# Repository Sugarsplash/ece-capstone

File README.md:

# ece-capstone
Intel sponsored irrigation project.

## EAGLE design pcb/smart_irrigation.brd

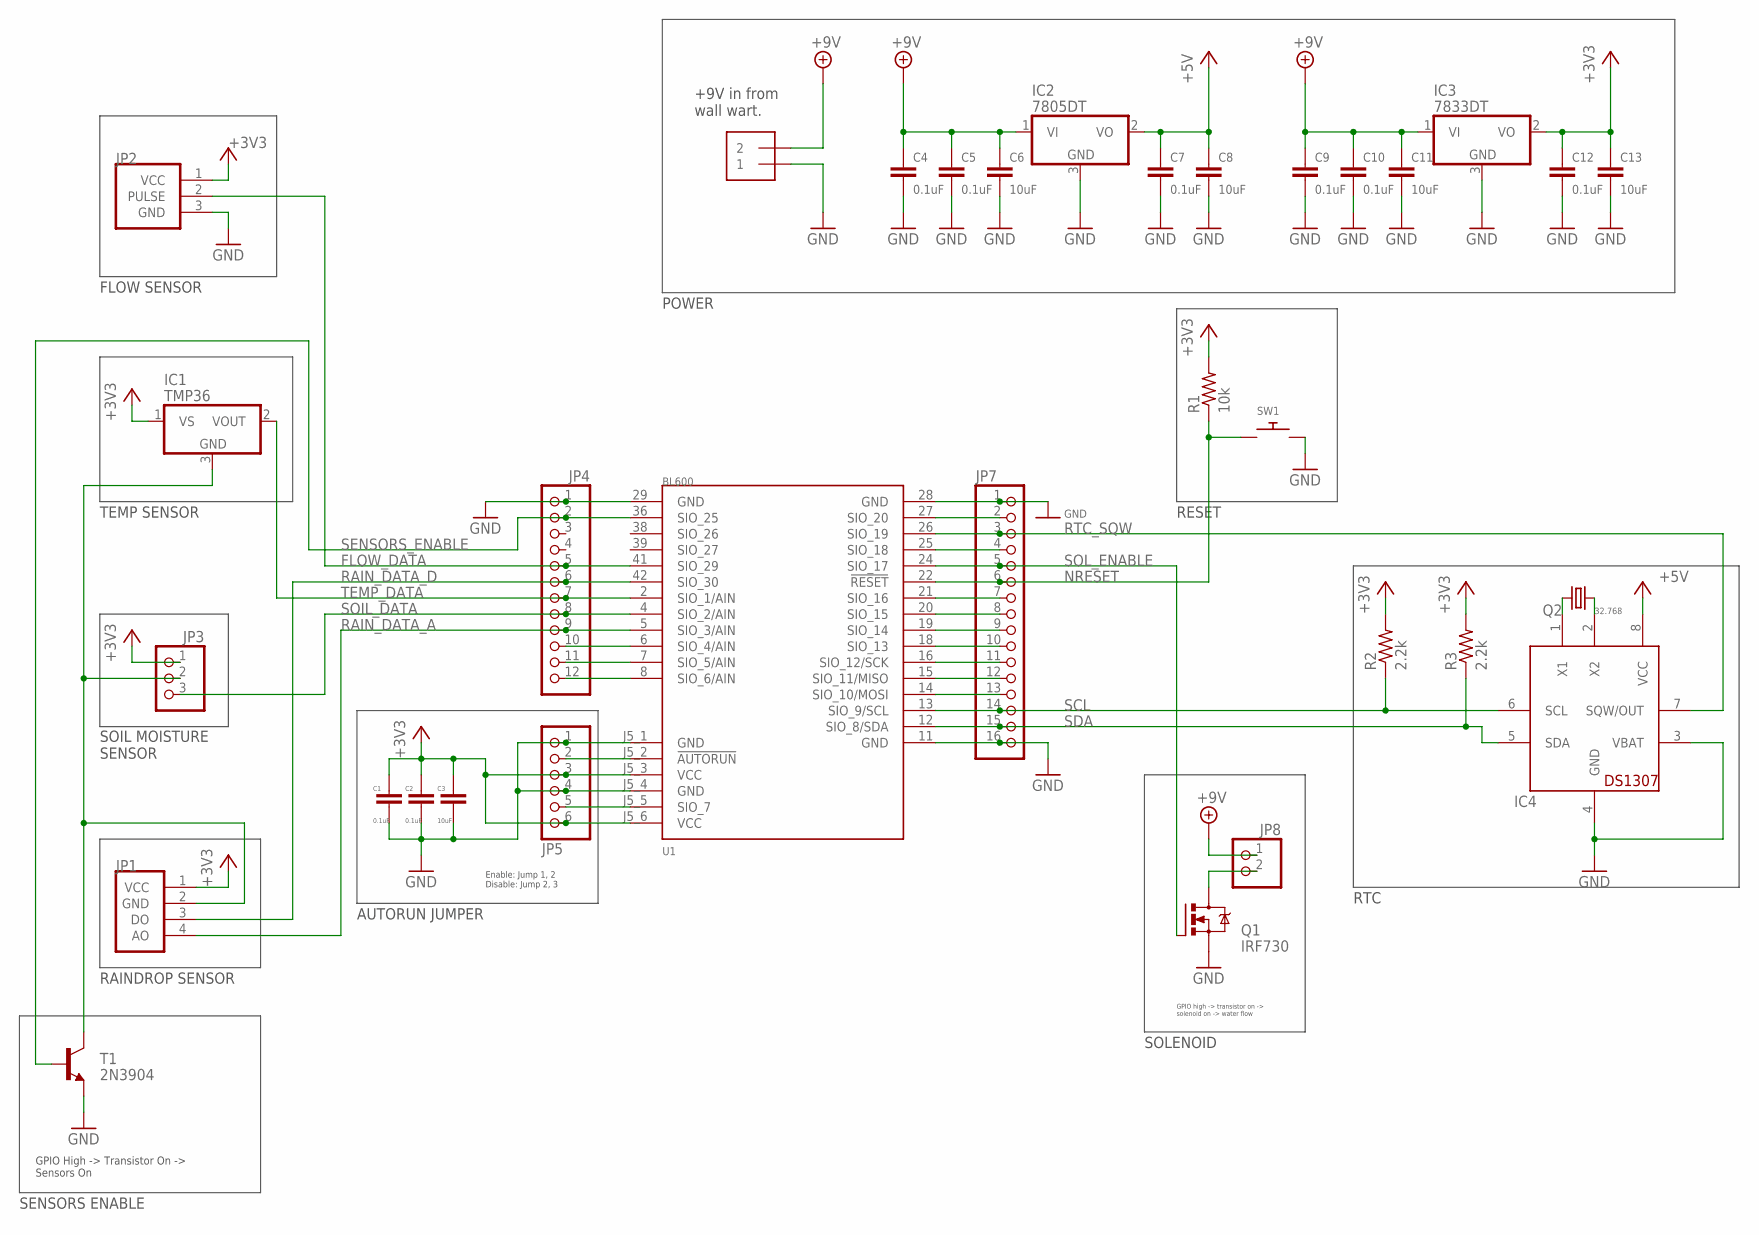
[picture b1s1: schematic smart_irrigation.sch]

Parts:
C1, C2, C4, C5, C7, C9, C10, C12: 0.1uF; C0805
C3, C6, C8, C11, C13: 10uF; C0805
IC1: TMP36; TO92
IC2: 7805DT; TO252
IC3: 7833DT; TO252
IC4: DS1307; DIL08
JP1: RAINDROP; 1X04
JP2: FLOW; 1X03
JP3: PINHD-1X3; 1X03
JP4: PINHD-1X12; 1X12
JP5: PINHD-1X6; 1X06
JP6: 1X2-3.5MM
JP7: PINHD-1X16; 1X16
JP8: PINHD-1X2; 1X02
Q1: IRF730; TO220
Q2: 32.768; TC38H
R1: 10k; M0805
R2, R3: 2.2k; M0805
SW1: SWITCH_PUSHBUTTONEVQ-PE; TACT_PANA-EVQ
T1: 2N3904; TO92
U1: BL600; BOB

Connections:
3V3_TRAN_COL: IC1.3 (GND), JP1.2 (GND), JP3.2, T1.1 (C)
+3V3: C1.1, C2.1, C3.1, C12.1, C13.1, IC1.1 (VS), IC3.2 (VO), JP1.1 (VCC), JP2.1 (VCC), JP3.1, JP5.3, JP5.6, R1.2, R2.2, R3.2, U1.J5_3 (VCC), U1.J5_6 (VCC)
+5V: C7.1, C8.1, IC2.2 (VO), IC4.8 (VCC)
+9V: C4.1, C5.1, C6.1, C9.1, C10.1, C11.1, IC2.1 (VI), IC3.1 (VI), JP6.2, JP8.1
FLOW_DATA: JP2.2 (PULSE), JP4.5, U1.41 (SIO_29)
GND: C1.2, C2.2, C3.2, C4.2, C5.2, C6.2, C7.2, C8.2, C9.2, C10.2, C11.2, C12.2, C13.2, IC2.3 (GND), IC3.3 (GND), IC4.3 (VBAT), IC4.4 (GND), JP2.3 (GND), JP4.1, JP5.1, JP5.4, JP6.1, JP7.1, JP7.16, Q1.S, SW1.P$2, T1.3 (E), U1.11 (GND), U1.28 (GND), U1.29 (GND), U1.J5_1 (GND), U1.J5_4 (GND)
unnamed: IC4.1 (X1), Q2.2
unnamed: IC4.2 (X2), Q2.1
NAUTORUN: JP5.2, U1.J5_2 (!AUTORUN)
NRESET: JP7.6, R1.1, SW1.P$1, U1.22 (!RESET)
RAIN_DATA_A: JP1.4 (AO), JP4.9, U1.5 (SIO_3/AIN)
RAIN_DATA_D: JP1.3 (DO), JP4.6, U1.42 (SIO_30)
RTC_SQW: IC4.7 (SQW/OUT), JP7.3, U1.26 (SIO_19)
SCL: IC4.6 (SCL), JP7.14, R2.1, U1.13 (SIO_9/SCL)
SDA: IC4.5 (SDA), JP7.15, R3.1, U1.12 (SIO_8/SDA)
SENSORS_ENABLE: JP4.2, T1.2 (B), U1.36 (SIO_25)
SIO_4: JP4.10, U1.6 (SIO_4/AIN)
SIO_5: JP4.11, U1.7 (SIO_5/AIN)
SIO_6: JP4.12, U1.8 (SIO_6/AIN)
SIO_7: JP5.5, U1.J5_5 (SIO_7)
SIO_10/MOSI: JP7.13, U1.14 (SIO_10/MOSI)
SIO_11/MISO: JP7.12, U1.15 (SIO_11/MISO)
SIO_12/SCK: JP7.11, U1.16 (SIO_12/SCK)
SIO_13: JP7.10, U1.18 (SIO_13)
SIO_14: JP7.9, U1.19 (SIO_14)
SIO_15: JP7.8, U1.20 (SIO_15)
SIO_16: JP7.7, U1.21 (SIO_16)
SIO_18: JP7.4, U1.25 (SIO_18)
SIO_20: JP7.2, U1.27 (SIO_20)
SOIL_DATA: JP3.3, JP4.8, U1.4 (SIO_2/AIN)
SOL_DRAIN: JP8.2, Q1.D
SOL_ENABLE: JP7.5, Q1.G, U1.24 (SIO_17)
TEMP_DATA: IC1.2 (VOUT), JP4.7, U1.2 (SIO_1/AIN)

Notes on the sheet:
+9V in from wall wart.
POWER
Enable: Jump 1, 2 Disable: Jump 2, 3
AUTORUN JUMPER
RTC
TEMP SENSOR
SOIL MOISTURE SENSOR
RAINDROP SENSOR
SOLENOID
GPIO high -> transistor on -> solenoid on -> water flow
SENSORS ENABLE
GPIO High -> Transistor On -> Sensors On
FLOW SENSOR
RESET

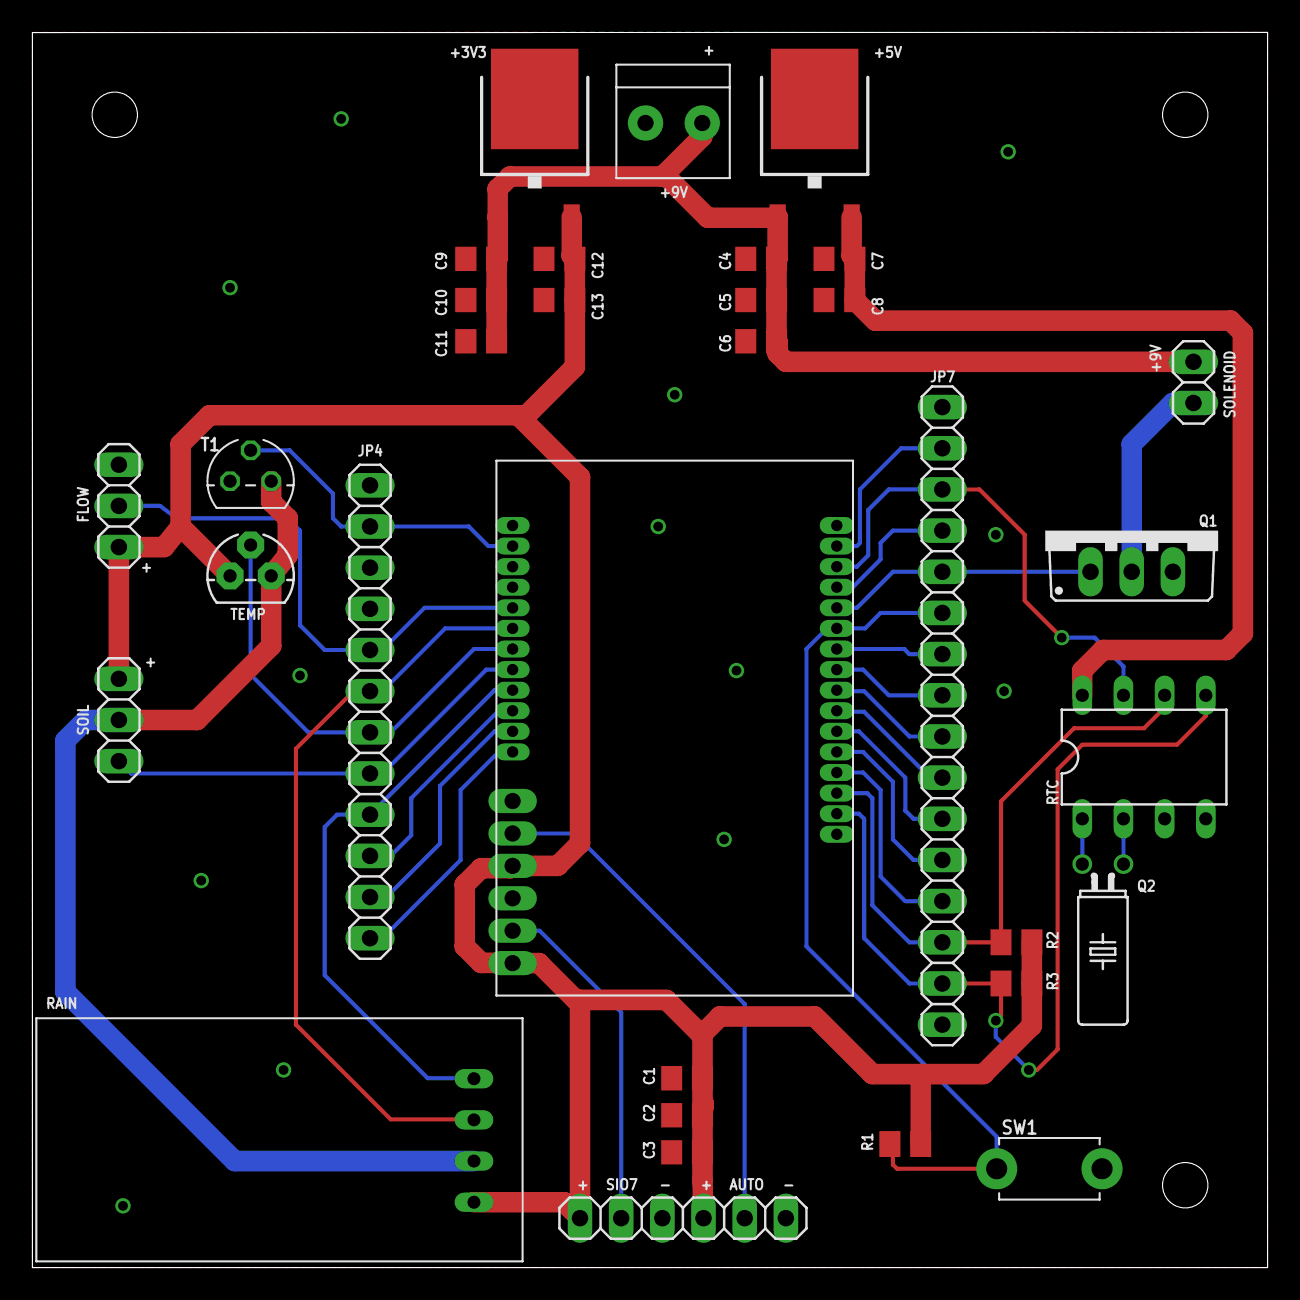
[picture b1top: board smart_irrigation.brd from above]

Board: 2 copper layers, 76.2 x 76.2 mm, 33 parts (0 on the bottom side), 33 nets.

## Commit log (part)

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2015-12-13 Initial irrigation scheduling research
2015-12-13 Add link to FAO paper
2015-12-28 Add additional research article stubs for reference
2016-01-07 Add logbook containing irrigation policy exploration.
2016-01-07 Add meeting notes folder
2016-01-10 Add research
2016-01-12 Add meeting notes from January 11th.
2016-01-15 Add notes for January 15.
2016-01-15 Article and code for BL600 module
    This folder contains the Elektor magazine articles and source code for
    the BL600-eBoB. The BL600_eBoB is a breakout board for the Laird
    Technology Bluetooth LE communication module.
2016-02-01 Add original black box diagrams for solenoid and flow sensor.
2016-02-01 Now with pdf!
2016-02-01 More more more.
2016-02-01 nvr gunna stopz
2016-02-02 Add BL600 black box diagram
2016-02-02 Replace deleted black box diagram
    Accidentally overwrote the temperature sensor diagram.
2016-02-02 Added RTC Blackboxes
2016-02-02 Updated RTC Blackboxes
2016-02-02 Update design model
2016-02-07 Add smartBASIC User Guide to doc folder
    The User Guide is the sole reference for instructions on how to write
    code in the language.
2016-02-08 Update documentation.
2016-02-08 Add src directory and flowTst.sb
2016-02-15 Add code to test solenoid circuit.
2016-02-15 Add datasheets directory.
2016-02-15 Update system design model.
2016-02-15 Add bl600 documentation.
2016-02-15 Add schematic to timeline
2016-02-15 Add temperature sensor block diagram
2016-02-17 Add initial app source
2016-02-17 Remove sponsor materials zip
2016-02-18 App: Add basic layout with input fields
2016-02-18 App: Implement Get button for Latitude
    Latitude can be automatically retrieved if desired rather than entered manually.
2016-02-18 App: Remove settings button
2016-02-18 App: Add app name to toolbar
2016-02-18 App: Round latitude to two decimal places
2016-02-18 App: Add dropdown with different units for area
2016-02-18 App: Use strings from strings.xml
2016-02-18 App: Separate activities for config and receive
    Main activity was split into different activities for configuration
    (latitude, date, area) of the irrigation system and receiving data from
    it.
2016-02-19 Added RTC Datasheet and Setup Instructions
2016-02-23 Change RTC in design docs to 5V VCC
2016-02-23 Add meeting notes. Modified timeline
2016-02-23 Add datasheet for temperature sensor
2016-02-24 Add website information for components without datasheets
2016-02-29 LDO Voltage Regulator Datasheet
2016-02-29 Text File of Regulators
2016-02-29 Add algorithm implemented in C.
2016-03-01 Add meeting notes February 29th
2016-03-05 Add initial SmartBasic version of algorithm. Implemented LUT and trigonomic functions
2016-03-05 Updated schematic. Added connections
2016-03-18 Initial BLE routine
    Skeleton for BLE routine sets up the BLE framework, configures status
    LEDs and advertising button, and is configured to be able to receive
    data: date, latitude, area.
2016-03-19 Add build files to .gitignore
2016-03-22 Updated wiring
2016-03-23 Rename "schematic" dir to "pcb"
2016-03-23 Create EAGLE library with BL600 BOB
2016-03-23 Add initial PCB files with power supply
2016-03-23 Remove programming pins from BL600 device
    The pins will have a header soldered onto them directly which will not
    be soldered onto the PCB itself.
2016-03-23 Add BL600 with autorun jumper to PCB
    The autorun jumper is used to enable and disable the autorun feature of
    the BL600.
2016-03-23 Rename EAGLE library file
    Schematic and board files updated to use new library filename
2016-03-23 Add temp EAGLE files to .gitignore
2016-03-23 PCB: Add RTC
2016-03-23 PCB: Add temp sensor
2016-03-23 PCB: Add soil moisture sensor
2016-03-23 PCB: Add caps across BL600 power input
2016-03-23 PCB: Add solenoid and flow sensor
2016-03-24 PCB: Add transistor to toggle sensors
2016-03-24 PCB: Initial board layout
2016-03-24 PCB: Approve ERC warnings/errors
2016-03-24 PCB: Give names to all signals.
2016-03-25 RTC driver and Analog drivers
2016-03-30 PCB: Fix spacing between headers on BL600 package
2016-03-30 PCB: Move terminal block farther into board
2016-03-30 PCB: Add reset button
2016-03-31 PCB: Change sensor pin assignments
    All digital sensor outputs are now in one cluster and all analog sensor
    outputs are in another cluster.
2016-03-31 Changed GPIO pin locations to match new schematic
2016-03-31 Add info on I2C functions
2016-04-01 Replace hardcoded pin definitions with macros
2016-04-01 Replace hardcoded GPIO functions with macros
2016-04-01 Remove extraneous temperature sensing file
2016-04-02 Move "library" files to lib directory
2016-04-02 Re-add ble.sb to repo
    Accidentally removed.
2016-04-02 Convert temperature code into function
2016-04-02 Convert soil moisture code into function
2016-04-06 Corrected sin function implementation. Added inverse cosine function
2016-04-07 Add meeting notes with advisor April 6th
2016-04-08 CC article on Transformers & Wall Warts
    This article is from Circuit Cellar magazine. It has a discussion on the circuitry in transformer-based wall warts. The article also mentions that the move is away from transformers to converters in 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
2016-04-10 Add development plan.
2016-04-15 PCB: Change SENSORS_ENABLE signal pin
    The BL600 breakout board includes SIO_26 and SIO_27, but they're
    reserved and unusable for some reason. SENSORS_ENABLE was thus changed
    from SIO_27 to SIO_25.
2016-04-15 PCB: Ground VBAT pin of RTC
    Per datasheet, if VBAT is unused, it must be grounded.
2016-04-15 PCB: Increase isolation from ground plane
2016-04-16 PCB: Reroute SDA and RTC_DATA lines
    They were precariously placed so that shorts could occur.
2016-04-18 First commit of FSM pseudo code. Looking for review from folks.
2016-04-18 Compiling sb code that does nothing.
2016-04-20 Add digital out states to gpio.sblib
    LOW=0, HIGH=1
2016-04-21 Correct typo in rain.sb
    rain_digital_read() not rain__digital_read()
2016-04-23 Remove old MOSFET test code
2016-04-23 Create event-driven main state machine
2016-04-23 Replace tabs with spaces
    Tabs are evil.
2016-04-24 PCB: Remove old schematic
2016-04-25 Add evapotranspiration calculations into main program.
2016-04-25 Fix typo in globals.sblib
2016-04-26 Get config values from BLE before Eto calculation
2016-04-26 Sample sensors and write to their characteristics
2016-04-27 Add functions for reading and writing to RTC.
2016-04-27 Clean up main.sb, add globals.
2016-04-28 App: Add ability to read all sensors
2016-04-28 App: Add ability to write config characteristics
2016-04-28 App: Move scan from options menu to main screen
2016-04-28 App: Remove default test files
2016-04-28 App: Convert latitude config value to integer
    Since the BL600 has no support for floats, the latitude value is
    multipled by 100 before being written to its characteristic.
    The size of the characteristic was also increased to 5 bytes.
2016-04-28 App: Add flood button
2016-04-28 Add flow signal to irrigate()
    When irrigate() turns the water on, it updates a characteristic so that
    the phone can see at any time if water is flowing. The signal is turned
    off when the water is turned off.
2016-04-28 App: Add text that tells whether water is flowing
2016-04-29 App: Add button for reading config values
    Previously the phone could only write config values, but it's
    advantageous to also be able to read the pre-existing configuration
    values.
2016-04-29 App: Change "GET" button to "Auto"
    The word "Get" was deceiving and might lead one to believe that its
    purpose was to get the value from the characteristic.
2016-04-29 App: Remove old menu code
    The menu used to have the Scan activity, but it was moved to the main
    activity, so the menu references were no longer needed.
2016-04-29 App: Rename buttons to be more explanatory
2016-04-29 App: Add "Scanning" toast
2016-05-02 Add historical data array with write and clear functions. Improved behavior of timer handlers.
2016-05-02 Initial correction to temperature conversion.
2016-05-02 Initial temp correction testing.
2016-05-02 Remove temperature test calls.
2016-05-02 Correct temperature conversion. Tested in refridgerator and room temp with calibrated thermometer.
2016-05-03 App: Remove unused area unit choices
    Area can be only entered in as either square meters or square feet
    because anything smaller doesn't make sense for the irrigation
    algorithm. The area is always written to the characteristic as square
    meters, however, and so it is converted first if entered as square feet.
    The smallest allowable area is 1 square meter and anything smaller will
    be rounded up to 1.
2016-05-03 Rearrange characteristic order in handler_char_val
    It was checking config characteristics, then the flood characteristic,
    then the final config characteristic, which was a mess.
2016-05-04 Moved config to handler_char_val
2016-05-05 Add meeting notes
2016-05-08 Remove rtc_read.sb
    No longer necessary
2016-05-09 Fixed compiler errors. This is the v0.8 source.
2016-05-09 Add ability to download stored data onto phone
    The phone is able to alert the device that it wishes to download any
    stored data with the History Signal characteristic. When the device
    receives that signal it begins to write data to the History
    characteristic (if any such data exists). The phone is alerted when that
    characterisitc has been updated via the Indicate property and it writes
    the data to a timestamped CSV file. The device gets alerted that the
2016-05-09 Fix merge errors
2016-05-10 App: Display size of dataArray (in # of days)
    When "Read Sensors" is clicked, the "History" field is updated. "Read
    Sensors" button was chosen due to lack of space for a new button
    (and to avoid more clutter).
2016-05-10 App: Fix pre-discovery crash
    If a read of a characteristic was attempted before all of the
    characteristics had been discovered then the app would crash,
    so a flag was added that is set to True after service discovery
    and set to False when disconnected.
2016-05-10 Make history size characteristic notifiable
    The phone will now automatically update its display of how many
    days of history are available for downloading, rather than manually
    reading it. The location of the size has also been moved to the Download
    History button itself.
2016-05-10 App: Remove old content layout file
    It was left over from when there was a separate configuration activity.
2016-05-13 Update BL600 user guides
    Newest firmware is 1.8.88.0 and that's what's being used. The Core
    Functionality guide has also been updated.
2016-05-13 Add wet test for installation.
2016-05-13 Correct i2c read errors.
2016-05-13 Correct eto and flow values due to improper latitude and rotation conversion.
2016-05-13 App: Read last sampled sensor values after connect
2016-05-14 App: Read Sensors button signals to update sensors
    Previously the Read Sensors button would just get the sample values from
    the last hourly sampling, but it's more useful to be able to get
    current sensor values whenever you want.
2016-05-16 Modify wet test procedure.
2016-05-16 Turn off transistor after sampling from ble.sb
2016-05-16 Close i2c handle upon successful reads.
2016-05-18 Solid Works Box Parts
2016-05-19 Add meeting notes for May 18th
2016-05-21 New Box Design
2016-05-24 More Box Updates
2016-05-26 Add meeting notes with sponsor May 25th
2016-05-27 Add meeting notes with advisor May 27th
2016-05-29 App: Update JRE version
2016-05-29 Add poster to docs
2016-05-29 Remove wetTest
    Artifact of debugging and no longer needed.
2016-05-29 Rename main.sb to be autorun-able
    The BL600 will automatically run any program at boot if its name is
    prepended with "$autorun$" and the AUTORUN pin is set LOW.
    The device should automatically start its routine at boot so it must be
    renamed.
2016-05-29 Clean up documents
2016-06-03 Added LED Support
2016-06-05 Made Things Better
